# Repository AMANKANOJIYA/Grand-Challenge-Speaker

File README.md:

# Grand-Challenge-Speaker
The main objective of this grand challenge was to energize young minds and develop indigenous innovative 
commercially viable product designs which can be up- scaled further under a Centre of Excellence being 
setup by Centre for Development of Advanced Computing (CDAC).
# P-004: To design low-cost Bluetooth Speaker
Wireless speakers are loudspeakers that receive audio signals using radio frequency (RF) waves
rather than over audio cables. Bluetooth technology is used to transmit audio data to the receiving
speaker. Expected features are easy pairing and noise cancellation.

### Speaker Full Schematic
</img>

### Speaker Main Schematic
</img>

### Speaker Charging + Speaker Schematic
</img>

## PCB Design 
</img>

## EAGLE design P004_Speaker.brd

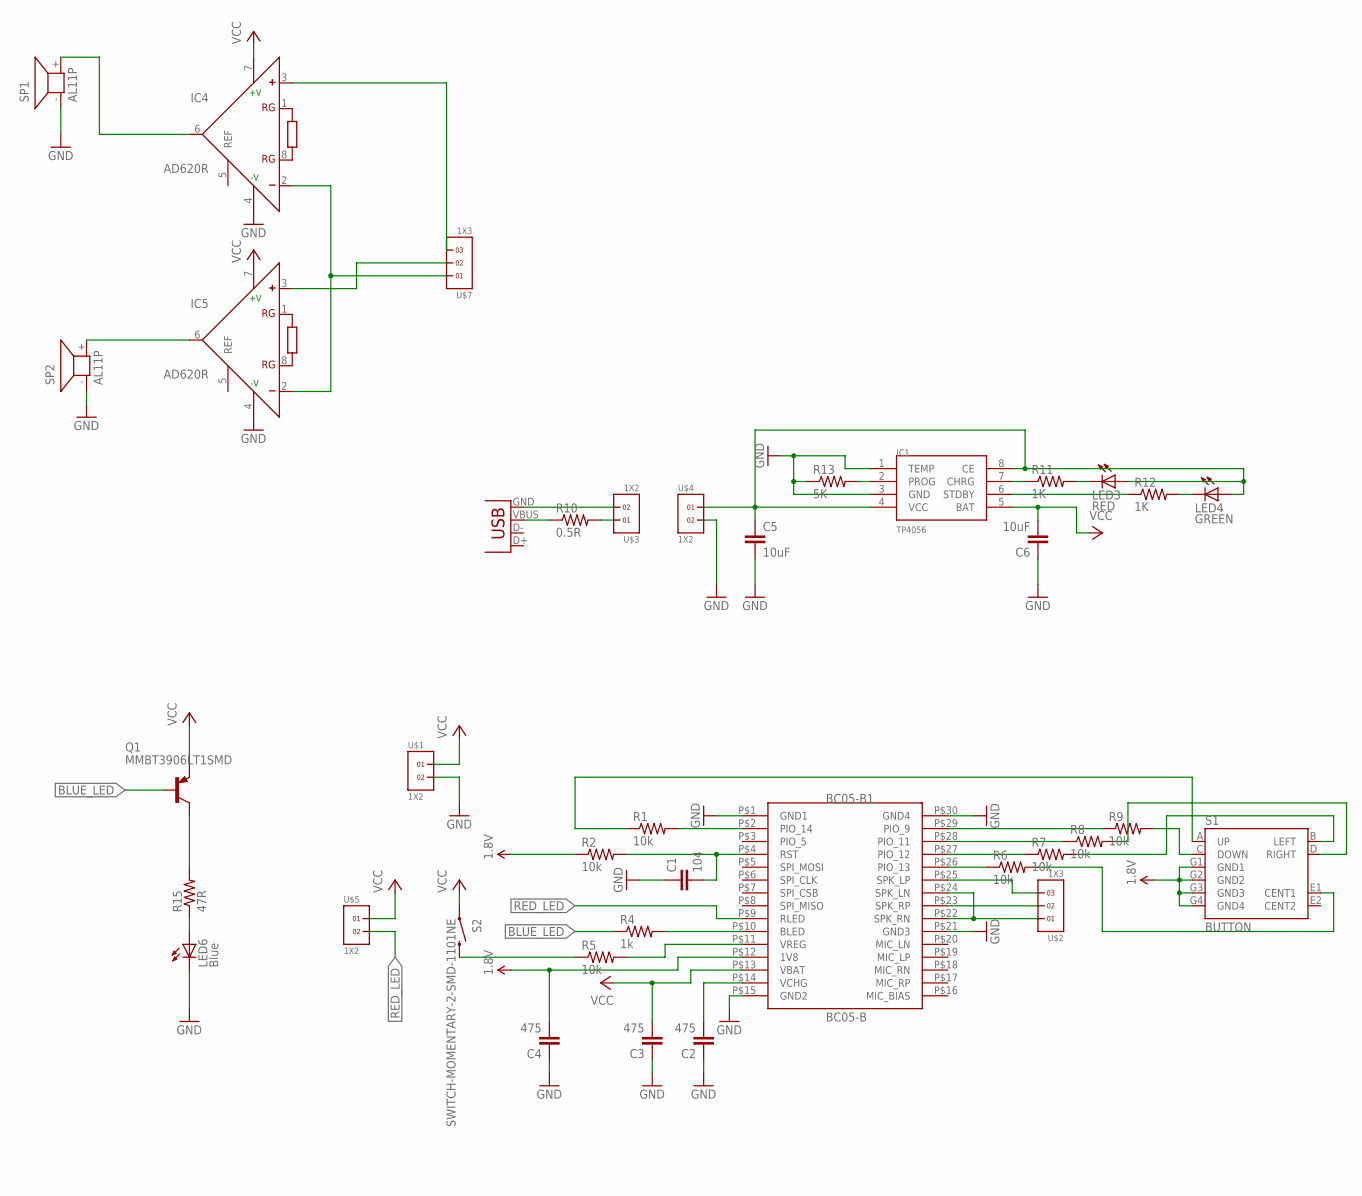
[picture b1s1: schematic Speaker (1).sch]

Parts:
BC05-B1: BC05-B
C1: 104; C0603K
C2, C3, C4: 475; C0603K
C5, C6: 10uF; C0805K
IC1: TP4056; SOP-8
IC4, IC5: AD620R; SO8
LED3: RED; CHIP-LED0805
LED4: GREEN; CHIP-LED0805
LED6: Blue; CHIP-LED0805
Q1: MMBT3906LT1SMD; SOT23-BEC
R1, R2, R5, R6, R7, R8, R9: 10k; R0603
R4: 1k; R0603
R10: 0.5R; M0805
R11, R12: 1K; R0603
R13: 5K; R0603
R15: 47R; R0603
S1: BUTTON
S2: SWITCH-MOMENTARY-2-SMD-1101NE; TACTILE-SWITCH-1101NE
SP1, SP2: AL11P
U$1, U$3, U$4, U$5: 1X2
U$2, U$7: 1X3
X1: USB-MICROB

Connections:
1.8V: BC05-B1.P$12 (1V8), C4.2, R2.1, S1.G1 (GND1), S1.G2 (GND2), S1.G3 (GND3), S1.G4 (GND4)
BLUE_LED: Q1.B, R4.1
GND: BC05-B1.P$1 (GND1), BC05-B1.P$15 (GND2), BC05-B1.P$21 (GND3), BC05-B1.P$30 (GND4), C1.1, C2.1, C3.1, C4.1, C5.2, C6.1, IC1.1 (TEMP), IC1.3 (GND), IC4.4 (-V), IC5.4 (-V), LED6.C, R13.1, SP1.- (1), SP2.- (1), U$1.2, U$4.2
unnamed: BC05-B1.P$2 (PIO_14), R1.2
unnamed: BC05-B1.P$4 (RST), C1.2, R2.2
unnamed: BC05-B1.P$11 (VREG), R5.2
unnamed: BC05-B1.P$10 (BLED), R4.2
unnamed: IC4.2 (-), IC5.2 (-), U$7.1
unnamed: BC05-B1.P$23 (SPK_RP), U$2.2
unnamed: BC05-B1.P$29 (PIO_9), R9.1
unnamed: BC05-B1.P$28 (PIO_11), R8.1
unnamed: BC05-B1.P$27 (PIO_12), R7.1
unnamed: BC05-B1.P$26 (PIO_13), R6.1
unnamed: R7.2, S1.B (LEFT)
unnamed: R8.2, S1.D (RIGHT)
unnamed: R6.2, S1.E1 (CENT1)
unnamed: R10.2, U$3.1
unnamed: R1.1, S1.A (UP)
unnamed: R5.1, S2.P$2 (2)
unnamed: BC05-B1.P$25 (SPK_LP), U$2.3
unnamed: BC05-B1.P$14 (VCHG), C2.2
unnamed: BC05-B1.P$22 (SPK_RN), BC05-B1.P$24 (SPK_LN), U$2.1
unnamed: R10.1, X1.VBUS
unnamed: C5.1, IC1.4 (VCC), IC1.8 (CE), LED3.A, LED4.A, U$4.1
unnamed: IC1.7 (CHRG), R11.1
unnamed: LED3.C, R11.2
unnamed: LED4.C, R12.2
unnamed: IC1.6 (STDBY), R12.1
unnamed: IC5.3 (+), U$7.2
unnamed: IC1.2 (PROG), R13.2
unnamed: LED6.A, R15.1
unnamed: IC4.3 (+), U$7.3
unnamed: R9.2, S1.C (DOWN)
unnamed: U$3.2, X1.GND
unnamed: Q1.C, R15.2
unnamed: IC4.6 (OUT), SP1.+ (2)
unnamed: IC5.6 (OUT), SP2.+ (2)
RED_LED: BC05-B1.P$9 (RLED), U$5.2
VCC: BC05-B1.P$13 (VBAT), C3.2, C6.2, IC1.5 (BAT), IC4.7 (+V), IC5.7 (+V), Q1.E, S2.P$1 (1), U$1.1, U$5.1

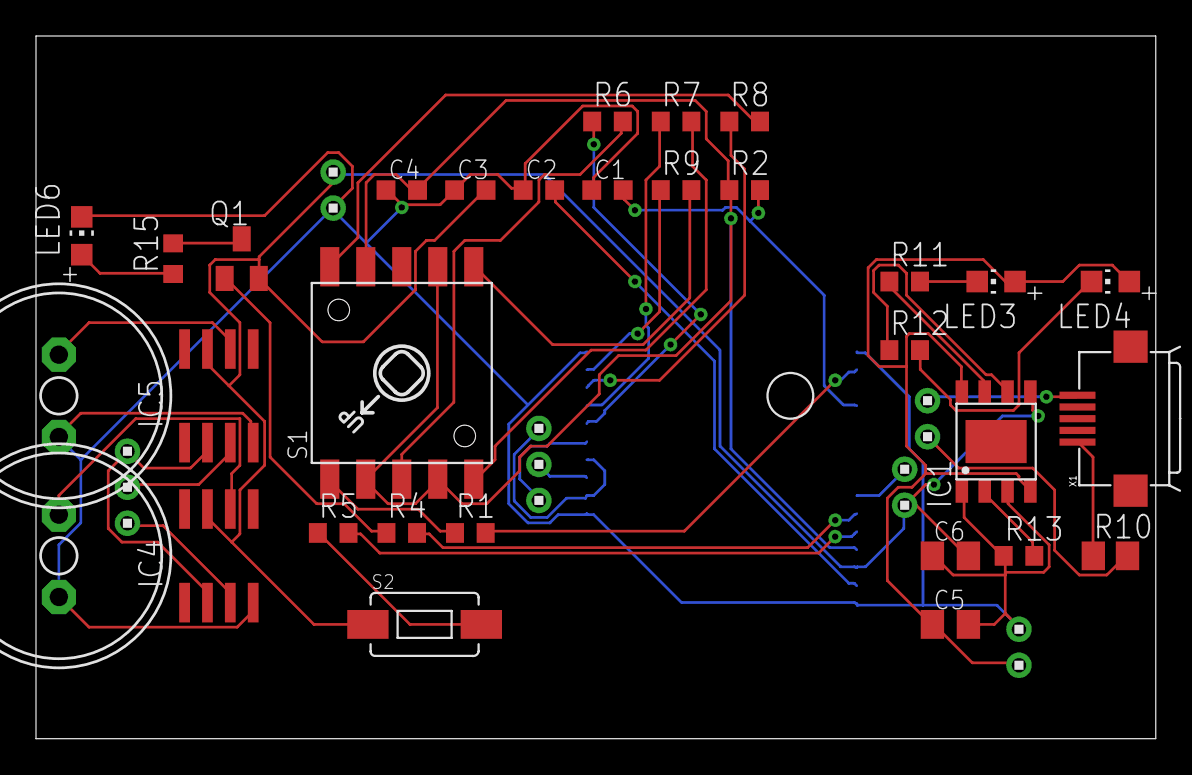
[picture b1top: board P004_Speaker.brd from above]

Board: 2 copper layers, 62.2 x 39.0 mm, 38 parts (0 on the bottom side), 39 nets.

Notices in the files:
parts and their libraries:
SparkFun-Electromechanical: Licensing: CC v3.0 Share-Alike You are welcome to use this library for commercial purposes.
